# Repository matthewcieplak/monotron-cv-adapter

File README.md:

# monotron-cv-adapter
A eurorack control voltage to Korg Monotron CV adapter PCB.

Includes inputs for a PITCH and GATE, and combined PITCH/GATE output that goes to the Monotron's "Gate" mod input.

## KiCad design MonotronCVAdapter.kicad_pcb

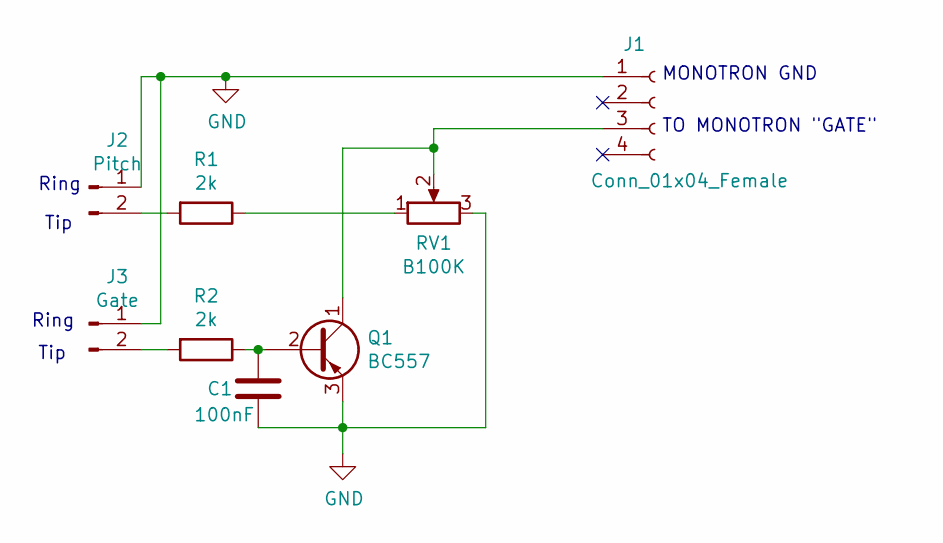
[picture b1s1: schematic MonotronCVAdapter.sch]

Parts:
C1: 100nF; CP_Radial_D5.0mm_P2.50mm
J1: Conn_01x04_Female; Pin_Header_Straight_1x04_Pitch2.54mm
J2: Pitch; Pin_Header_Straight_1x02_Pitch2.54mm
J3: Gate; Pin_Header_Straight_1x02_Pitch2.54mm
Q1: BC557; TO-92_Inline_Wide
R1, R2: 2k; R_Axial_DIN0207_L6.3mm_D2.5mm_P10.16mm_Horizontal
RV1: B100K; Potentiometer_Omeg_PC16PU_Horizontal

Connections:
GND: C1.2, J1.1, J2.1, J3.1, Q1.3 (E), RV1.3
unnamed: C1.1, Q1.2 (B), R2.1
unnamed: J1.3, Q1.1 (C), RV1.2
unnamed: J2.2, R1.2
unnamed: J3.2, R2.2
unnamed: R1.1, RV1.1

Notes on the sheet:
Tip
Ring
MONOTRON GND
TO MONOTRON "GATE"

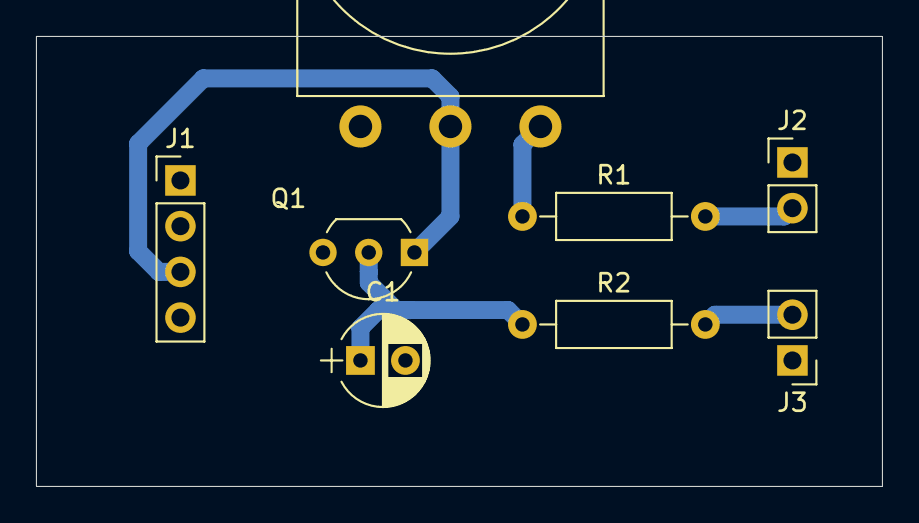
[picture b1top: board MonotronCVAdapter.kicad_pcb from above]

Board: 2 copper layers, 47.0 x 25.0 mm, 8 parts (0 on the bottom side), 6 nets.

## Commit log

2019-07-09 Adding PDF of schematic
2019-09-17 Adding PDF combined layers
